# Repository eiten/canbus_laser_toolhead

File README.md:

# 🔥 Laser CANbus Toolhead PCB

> 🌍 **Languages:** [English](README.md) | [Deutsch](README.de.md)

A compact, robust toolhead board for Klipper-based laser engravers and cutters (CoreXY). This board integrates power supply, laser driver logic, CAN-Bus communication, and input shaping (ICM-20602) in the smallest possible space.

## 📚 Contents

<!-- @import "[TOC]" {cmd="toc" depthFrom=1 depthTo=6 orderedList=false} -->

<!-- code_chunk_output -->

- [🔥 Laser CANbus Toolhead PCB](#-laser-canbus-toolhead-pcb)
  - [📚 Contents](#-contents)
  - [✨ Features](#-features)
    - [🧠 Microcontroller](#-microcontroller)
    - [🔗 CAN-Bus Communication](#-can-bus-communication)
    - [📊 Input Shaping](#-input-shaping)
    - [⚡ Laser Power Control](#-laser-power-control)
    - [🎛️ Laser Signal Control](#️-laser-signal-control)
    - [🔌 Power Supply](#-power-supply)
    - [🚨 Diagnostics & Monitoring](#-diagnostics--monitoring)
  - [📋 Klipper Configuration](#-klipper-configuration)
    - [Basic MCU Setup](#basic-mcu-setup)
    - [Input Shaping (ICM-20602)](#input-shaping-icm-20602)
    - [Laser Control](#laser-control)
  - [🔌 Pinout & Connector Assignment](#-pinout--connector-assignment)
    - [J101 - Power & CAN Input (Micro-Fit 3.0, 2x2, THT)](#j101---power--can-input-micro-fit-30-2x2-tht)
    - [J102 - Laser Output (Micro-Fit 3.0, 1x3, THT)](#j102---laser-output-micro-fit-30-1x3-tht)
    - [Debug/Programming Header (Back Side)](#debugprogramming-header-back-side)
  - [🔧 Installation & Setup](#-installation--setup)
    - [1. CAN-Bus Configuration](#1-can-bus-configuration)
    - [2. Firmware Flash](#2-firmware-flash)
    - [3. Find UUID](#3-find-uuid)
  - [⚠️ Safety Notes](#️-safety-notes)
  - [🛠️ BOM (Bill of Materials) - Highlights](#️-bom-bill-of-materials---highlights)
  - [🛠️ Technical Specifications](#️-technical-specifications)
  - [📝 Changelog](#-changelog)
    - [Rev. 1](#rev-1)
    - [Rev. 0 (Initial Release)](#rev-0-initial-release)
  - [📚 Additional Resources](#-additional-resources)
  - [License](#license)

<!-- /code_chunk_output -->

## ✨ Features

### 🧠 Microcontroller
- **MCU:** STM32F072CBU6 (Cortex-M0, 48MHz, CAN-capable)
- **Stability:** 12MHz crystal for maximum CAN-Bus stability
- **Firmware:** Klipper-compatible

### 🔗 CAN-Bus Communication
- **Transceiver:** SN65HVD230 with ESD protection
- **Termination:** Split termination via solder jumper
- **Slope Control:** Switchable for EMI optimization

### 📊 Input Shaping
- **Sensor:** On-board ICM-20602 accelerometer/gyroscope (SPI)
- **Purpose:** Klipper resonance measurement for perfect print quality
- **Advantage:** Better availability and modern sensor technology

### ⚡ Laser Power Control
- **Circuit:** 24V / 6A High-Side Switch (CJAC70P06 P-MOSFET, 60V rated)
- **Peak Current:** 8A capability
- **Soft-Start:** Limits inrush current (Rise-time ~1.2ms)
- **Safety:** Hardware pull-down prevents unwanted activation
- **Limitation:** Max 6A limited by Micro Fit 3.0 connector with 0.75mm² wire

### 🎛️ Laser Signal Control
- **PWM:** 5V Level-shifted via 74AHCT1G125 buffer
- **Quality:** Clean edges, true hardware PWM via STM32 timer
- **Compatibility:** Common diode lasers

### 🔌 Power Supply
- **Input:** 24V with 250mA PTC fuse and SMF24A TVS diode
- **5V Rail:** MP2459 Buck converter (up to 60V input tolerant)
- **3.3V Rail:** XC6206 LDO for MCU and peripherals

### 🚨 Diagnostics & Monitoring
- **Power LEDs:** 24V In, 24V Sys, 5V, 3.3V
- **Status LEDs:** Laser Enable, Laser PWM, Heartbeat

## 📋 Klipper Configuration

### Basic MCU Setup
```ini
[mcu toolhead]
canbus_uuid: <your-uuid>  # Find with "ls /dev/serial/by-id/*" or "~/klippy-env/bin/python ~/klipper/scripts/canbus_query.py can0"

[temperature_sensor toolhead_mcu]
sensor_type: temperature_mcu
sensor_mcu: toolhead
```

### Input Shaping (ICM-20602)
```ini
[mpu9250]
cs_pin: toolhead:PA4
spi_bus: spi1
#axes_map: x,y,z  # Configure according to your printer orientation

[resonance_tester]
accel_chip: mpu9250
probe_points:
    150, 150, 20  # Adjust to your bed size
```

### Laser Control
```ini
# Laser PWM Signal
[output_pin laser_pwm]
pin: toolhead:PB14
pwm: True
cycle_time: 0.001          # 1kHz PWM frequency
shutdown_value: 0          # Safety: laser off during emergency

# Laser Enable (optional)
[output_pin laser_enable]
pin: toolhead:PB15
value: 0
shutdown_value: 0

# Heartbeat LED (optional)
[output_pin heartbeat]
pin: toolhead:PA9
pwm: True
cycle_time: 1.0
```

## 🔌 Pinout & Connector Assignment

### J101 - Power & CAN Input (Micro-Fit 3.0, 2x2, THT)
| Pin | Signal | Description |
|-----|---------|-------------|
| 1 | **+24V** | Main power input (High Current) |
| 2 | **GND** | Ground |
| 3 | **CAN_H** | CAN-Bus High Signal |
| 4 | **CAN_L** | CAN-Bus Low Signal |

### J102 - Laser Output (Micro-Fit 3.0, 1x3, THT)
| Pin | Signal | Description |
|-----|---------|-------------|
| 1 | **GND** | Laser Ground |
| 2 | **PWM** | 5V PWM Signal (Level-Shifted) |
| 3 | **+24V** | Switched Laser Power (Soft-Start) |

### Debug/Programming Header (Back Side)
| Pad | Pin | Signal | Function |
|-----|-----|---------|----------|
| 1 | - | **5V** | 5V Supply (from Programmer) |
| 2 | - | **3.3V** | VTref (Reference Voltage) |
| 3 | PA13 | **SWDIO** | Serial Wire Debug I/O |
| 4 | PA14 | **SWCLK** | Serial Wire Debug Clock |
| 5 | - | **NRST** | Reset Signal |
| 6 | - | **GND** | Ground |

> **💡 Bootloader Mode:** To force the STM32 into DFU/Bootloader mode (e.g., for initial flash with Katapult), bridge the **BOOT0** pad with **3.3V** during power-on.

## 🔧 Installation & Setup

### 1. CAN-Bus Configuration
- Set CAN-Bus termination according to position in network
- Baud rate: 1 Mbit/s (Klipper standard)

### 2. Firmware Flash
1. Put board into DFU mode (bridge BOOT0)
2. Compile Klipper for STM32F072 with CAN support
3. Flash firmware: `make flash FLASH_DEVICE=<dfu-device>`

### 3. Find UUID
```bash
~/klippy-env/bin/python ~/klipper/scripts/canbus_query.py can0
```

## ⚠️ Safety Notes

- **Laser Safety:** Always wear protective eyewear
- **Power Supply:** Only operate with 24V DC
- **Initial Setup:** Slowly ramp up laser power
- **Emergency:** Hardware pull-down ensures safe state

## 🛠️ BOM (Bill of Materials) - Highlights

| Component | Value/Type | Function | Package | Order Code |
|-----------|------------|----------|---------|------------|
| **U101** | STM32F072CBU6 | Main Microcontroller | UFQFPN-48 | STM32F072CBU6 |
| **U102** | MP2459GJ-Z | Buck Converter 24V→5V | TSOT-23-8 | MP2459GJ-Z |
| **U105** | SN65HVD230DR | CAN-Bus Transceiver | SOIC-8 | SN65HVD230DR |
| **U106** | ICM-20602 | 6-Axis IMU (Accelerometer/Gyroscope) | LGA-16 | ICM-20602 |
| **Q101** | CJAC70P06 | P-MOSFET (Laser Switch, 60V) | SOIC-8 | CJAC70P06 |
| **D101** | SMF24A | TVS Diode (Overvoltage Protection) | DO-214AC | SMF24A |
| **F101** | 1812L025 | PTC Fuse 250mA | 1812 | 1812L025 |
| **Y101** | 12MHz | Crystal for CAN Stability | HC-49/S | 12MHz Crystal |
| **J101/J102** | Micro-Fit 3.0 | THT Connectors | THT | Micro-Fit 3.0 THT |

## 🛠️ Technical Specifications

| Parameter | Value | Unit |
|-----------|-------|------|
| **Input Voltage** | 24 ± 2 | V |
| **Laser Current (max)** | 4 | A |
| **CAN Baud Rate** | 1 | Mbit/s |
| **PWM Frequency** | 1 | kHz |
| **Soft-Start Time** | ~1.2 | ms |
| **Operating Temperature** | -10 to +70 | °C |
| **Dimensions** | TBD | mm |

## 📝 Changelog

### Rev. 0.1
- **Transistor Upgrade:** Replaced MOSFET with CJAC70P06 (60V voltage rating)
- **Sensor Upgrade:** Changed from ADXL345 to ICM-20602 (better availability, modern 6-axis IMU)
- **Connector Change:** Micro Fit 3.0 connectors changed from SMD to THT mounting
- **Silkscreen Enhancement:** Added connector pin assignments to silkscreen for easier assembly
- **Layout Improvements:** Cleaned up component placement and optimized routing
- **Documentation:** Updated overview image to reflect current design
- **BOM Update:** Added component order numbers and updated production data
- **Production Files:** Updated assembly and production files with current components

### Rev. 0.0 (Initial Release)
- Initial PCB design with STM32F072CBU6 microcontroller
- CAN-Bus communication with SN65HVD230 transceiver
- 24V/4A laser power control with AO4407A MOSFET
- ADXL345 accelerometer for input shaping
- MP2459 buck converter for power supply

## 📚 Additional Resources

- [Klipper Documentation](https://www.klipper3d.org/Config_Reference.html)
- [CAN-Bus Setup Guide](https://www.klipper3d.org/CANBUS.html)
- [Input Shaping](https://www.klipper3d.org/Resonance_Compensation.html)
- [Katapult Firmware Flasher](https://github.com/Arksine/katapult)

## License

This project is licensed under the **Creative Commons Attribution-NonCommercial-ShareAlike 4.0 International License** (CC BY-NC-SA 4.0).

This means you are free to:
- **Share** — copy and redistribute the material in any medium or format
- **Adapt** — remix, transform, and build upon the material

Under the following terms:
- **Attribution** — You must give appropriate credit, provide a link to the license, and indicate if changes were made
- **NonCommercial** — You may not use the material for commercial purposes
- **ShareAlike** — If you remix, transform, or build upon the material, you must distribute your contributions under the same license

For the full license text, visit: https://creativecommons.org/licenses/by-nc-sa/4.0/

---

> **Note:** The original documentation is in German ([README.de.md](README.de.md)). This English version is a translation for international users.

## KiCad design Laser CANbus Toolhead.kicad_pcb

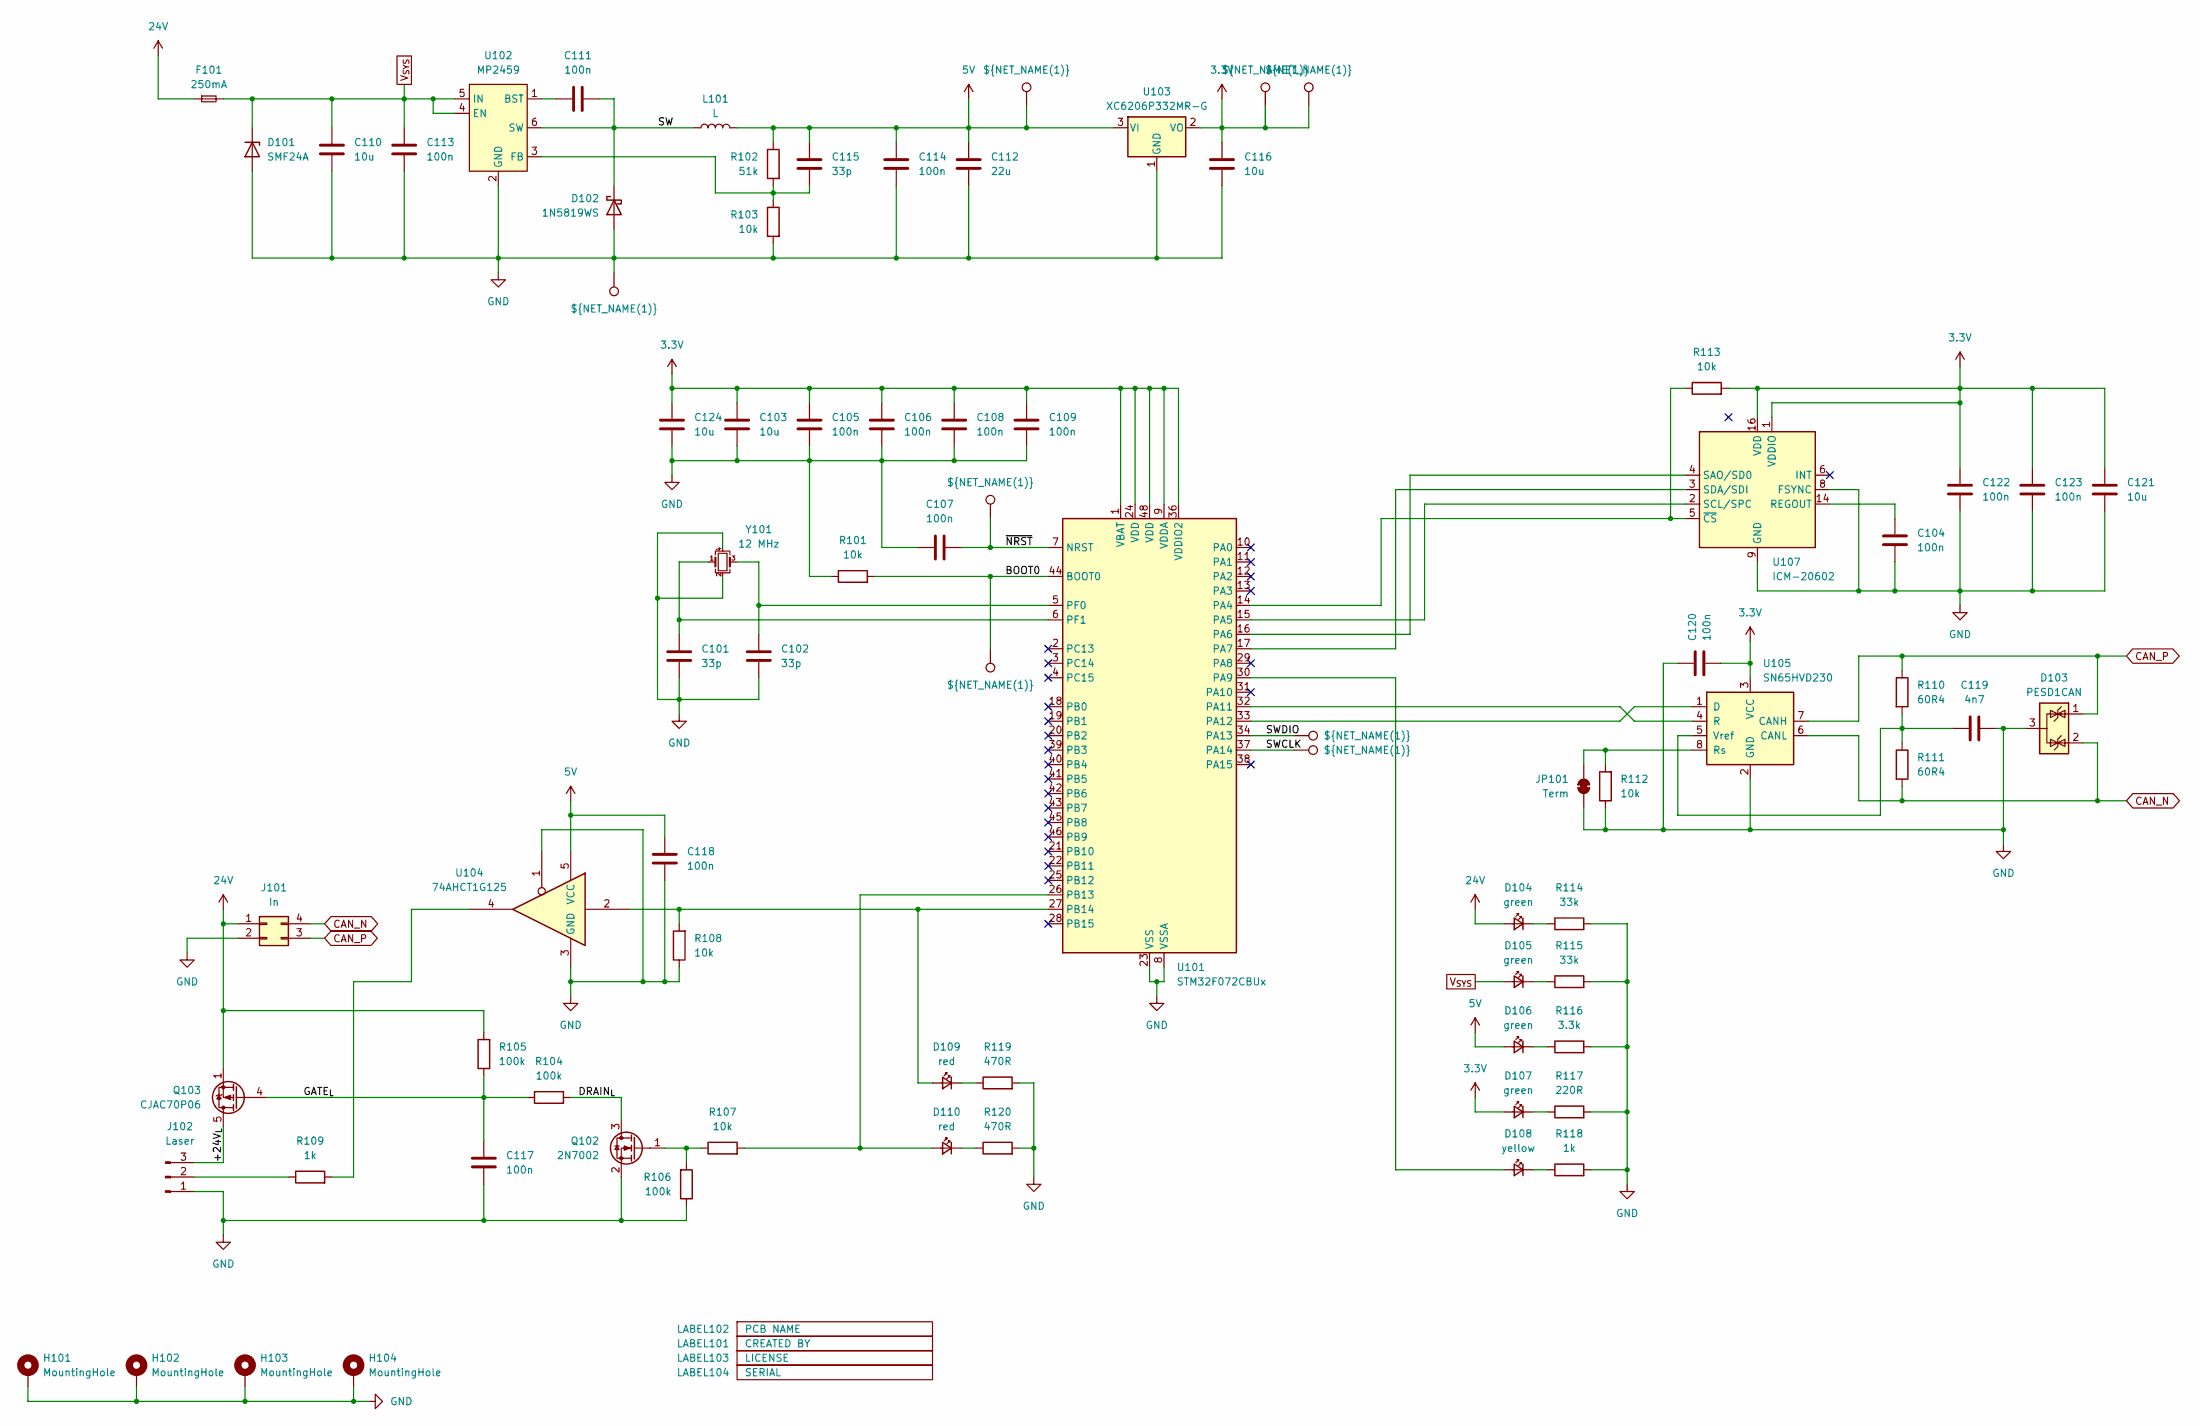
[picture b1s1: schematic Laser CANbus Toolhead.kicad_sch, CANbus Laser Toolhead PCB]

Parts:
C101, C102, C115: 33p; C_0402_1005Metric; Manufacturer Part # 0402CG330J500NT; LCSC Part # C1562
C103, C110, C116, C121, C124: 10u; C_0805_2012Metric; Manufacturer Part # GRM21BR61H106KE43L; LCSC Part # C440198
C104, C105, C106, C107, C108, C109, C111, C113, C114, C117, C118, C120, C122, C123: 100n; C_0402_1005Metric; Manufacturer Part # CL05B104KB54PNC; LCSC Part # C307331
C112: 22u; C_0805_2012Metric; Manufacturer Part # CL21A226MAQNNNE; LCSC Part # C45783
C119: 4n7; C_0402_1005Metric; Manufacturer Part # 0402B472K500NT; LCSC Part # C1538
D101: SMF24A; D_SOD-123F; Manufacturer Part # SMF24A; LCSC Part # C19077514
D102: 1N5819WS; D_SOD-323; Manufacturer Part # 1N5819WS; LCSC Part # C191023
D103: PESD1CAN; SOT-23; Manufacturer Part # PESD1CAN; LCSC Part # C343993
D104, D105, D106, D107: green; LED_0805_2012Metric; Manufacturer Part # KT-0805G; LCSC Part # C2297
D108: yellow; LED_0805_2012Metric; Manufacturer Part # KT-0805Y; LCSC Part # C2296
D109, D110: red; LED_0603_1608Metric; Manufacturer Part # KT-0603R; LCSC Part # C2286
F101: 250mA; Fuse_0805_2012Metric; Manufacturer Part # LUTE 0805L025/36XR; LCSC Part # C20608679
H101, H102, H103, H104: MountingHole; MountingHole_2.7mm_Pad_Via
J101: In; Molex_Micro-Fit_3.0_43045-0412_2x02_P3.00mm_Vertical; Manufacturer Part # M3025V-2x2P; LCSC Part # C492540
J102: Laser; Molex_Micro-Fit_3.0_43650-0315_1x03_P3.00mm_Vertical; Manufacturer Part # M3025V-1x3P; LCSC Part # C705183
JP101: Term; SolderJumper-2_P1.3mm_Bridged_RoundedPad1.0x1.5mm
L101: L; L_1008_2520Metric; Manufacturer Part # FTC252012S100MBCA; LCSC Part # C5832376
LABEL101: CREATED BY; EduardIten
LABEL102: PCB NAME; CLT Rev. xxx
LABEL103: LICENSE; CC_BY_NC_SA 4
LABEL104: SERIAL; SERIAL_No
Q102: 2N7002; SOT-23; Manufacturer Part # 2N7002; LCSC Part # C8545
Q103: CJAC70P06; AO_DFN-8-1EP_5.55x5.2mm_P1.27mm_EP4.12x4.6mm; Manufacturer Part # CJAC70P06; LCSC Part # C2898279
R101, R103, R107, R108, R112, R113: 10k; R_0402_1005Metric; Manufacturer Part # 0402WGF1002TCE; LCSC Part # C25744
R102: 51k; R_0402_1005Metric; Manufacturer Part # 0402WGF5102TCE; LCSC Part # C25794
R104, R105, R106: 100k; R_0402_1005Metric; Manufacturer Part # 0402WGF1003TCE; LCSC Part # C25741
R109, R118: 1k; R_0402_1005Metric; Manufacturer Part # 0402WGF1001TCE; LCSC Part # C11702
R110, R111: 60R4; R_0402_1005Metric; Manufacturer Part # 0402WGF604JTCE; LCSC Part # C60310
R114, R115: 33k; R_0402_1005Metric; Manufacturer Part # 0402WGF3302TCE; LCSC Part # C25779
R116: 3.3k; R_0402_1005Metric; Manufacturer Part # 0402WGF3301TCE; LCSC Part # C25890
R117: 220R; R_0402_1005Metric; Manufacturer Part # 0402WGF2200TCE; LCSC Part # C25091
R119, R120: 470R; R_0402_1005Metric; Manufacturer Part # 0402WGF4700TCE; LCSC Part # C25117
TP101, TP102, TP103, TP104, TP105, TP106, TP107, TP108: ${NET_NAME(1)}; NAMED_TEST_POINT
U101: STM32F072CBUx; QFN-48-1EP_7x7mm_P0.5mm_EP5.6x5.6mm; Manufacturer Part # STM32F072CBU6; LCSC Part # C92504
U102: MP2459; SOT-23-6; Manufacturer Part # MP2459GJ-Z; LCSC Part # C39578
U103: XC6206P332MR-G; SOT-23-3; Manufacturer Part # XC6206P332MR-G; LCSC Part # C5446
U104: 74AHCT1G125; SOT-353_SC-70-5; Manufacturer Part # SN74AHCT1G125DBVR; LCSC Part # C7484
U105: SN65HVD230; SOIC-8_3.9x4.9mm_P1.27mm; Manufacturer Part # SN65HVD230DR; LCSC Part # C12084
U107: ICM-20602; LGA-16_3x3mm_P0.5mm_LayoutBorder3x5y
Y101: 12 MHz; Crystal_SMD_3225-4Pin_3.2x2.5mm; Manufacturer Part # X322512MSB4SI; LCSC Part # C9002

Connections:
3.3V: C103.1, C105.1, C106.1, C108.1, C109.1, C116.1, C120.2, C121.1, C122.1, C123.1, C124.1, D107.2 (A), R113.2, TP102.1, TP108.1, U101.1 (VBAT), U101.9 (VDDA), U101.24 (VDD), U101.36 (VDDIO2), U101.48 (VDD), U103.2 (VO), U105.3 (VCC), U107.1 (VDDIO), U107.16 (VDD)
5V: C112.1, C114.1, C115.1, C118.1, D106.2 (A), L101.2, R102.1, TP101.1, U103.3 (VI), U104.5 (VCC)
24V: D104.2 (A), F101.1, J101.1, Q103.1 (S), Q103.2 (S), Q103.3 (S), R105.2
/+24V_{L}: J102.3, Q103.5 (D)
/BOOT0: R101.2, TP107.1, U101.44 (BOOT0)
/DRAIN_{L}: Q102.3 (D), R104.2
/GATE_{L}: C117.1, Q103.4 (G), R104.1, R105.1
/SW: C111.2, D102.1 (K), L101.1, U102.6 (SW)
/SWCLK: TP106.1, U101.37 (PA14)
/SWDIO: TP105.1, U101.34 (PA13)
/~NRST: C107.2, TP104.1, U101.7 (NRST)
CAN_N: D103.2 (K), J101.4, R111.2, U105.6 (CANL)
CAN_P: D103.1 (K), J101.3, R110.1, U105.7 (CANH)
GND: C101.2, C102.2, C103.2, C104.2, C105.2, C106.2, C107.1, C108.2, C109.2, C110.2, C112.2, C113.2, C114.2, C116.2, C117.2, C118.2, C119.2, C120.1, C121.2, C122.2, C123.2, C124.2, D101.2 (A), D102.2 (A), D103.3 (A), H101.1, H102.1, H103.1, H104.1, J101.2, J102.1, JP101.2 (B), Q102.2 (S), R101.1, R103.2, R106.1, R108.1, R112.1, R114.2, R115.2, R116.2, R117.2, R118.2, R119.2, R120.2, TP103.1, U101.8 (VSSA), U101.23 (VSS), U101.35 (VSS), U101.47 (VSS), U101.49 (VSS), U102.2 (GND), U103.1 (GND), U104.1, U104.3 (GND), U105.2 (GND), U107.8 (FSYNC), U107.9 (GND), U107.10 (GND), U107.11 (GND), U107.12 (GND), U107.13 (GND), U107.15 (GND), Y101.2, Y101.4
unnamed: D104.1 (K), R114.1
unnamed: D105.1 (K), R115.1
unnamed: D106.1 (K), R116.1
unnamed: D107.1 (K), R117.1
unnamed: D108.2 (A), U101.30 (PA9)
unnamed: D108.1 (K), R118.1
unnamed: D109.2 (A), R108.2, U101.27 (PB14), U104.2
unnamed: D109.1 (K), R119.1
unnamed: D110.2 (A), R107.2, U101.26 (PB13)
unnamed: D110.1 (K), R120.1
unnamed: J102.2, R109.1
unnamed: JP101.1 (A), R112.2, U105.8 (Rs)
unnamed: Q102.1 (G), R106.2, R107.1
unnamed: R109.2, U104.4
unnamed: R113.1, U101.14 (PA4), U107.5 (~CS)
unnamed: U101.15 (PA5), U107.2 (SCL/SPC)
unnamed: U101.16 (PA6), U107.4 (SAO/SD0)
unnamed: U101.17 (PA7), U107.3 (SDA/SDI)
unnamed: U101.32 (PA11), U105.4 (R)
unnamed: U101.33 (PA12), U105.1 (D)
unnamed: C102.1, U101.5 (PF0), Y101.3
unnamed: C101.1, U101.6 (PF1), Y101.1
unnamed: C111.1, U102.1 (BST)
unnamed: C115.2, R102.2, R103.1, U102.3 (FB)
unnamed: C119.1, R110.2, R111.1, U105.5 (Vref)
unnamed: C104.1, U107.14 (REGOUT)
V_{SYS}: C110.1, C113.1, D101.1 (K), D105.2 (A), F101.2, U102.4 (EN), U102.5 (IN)

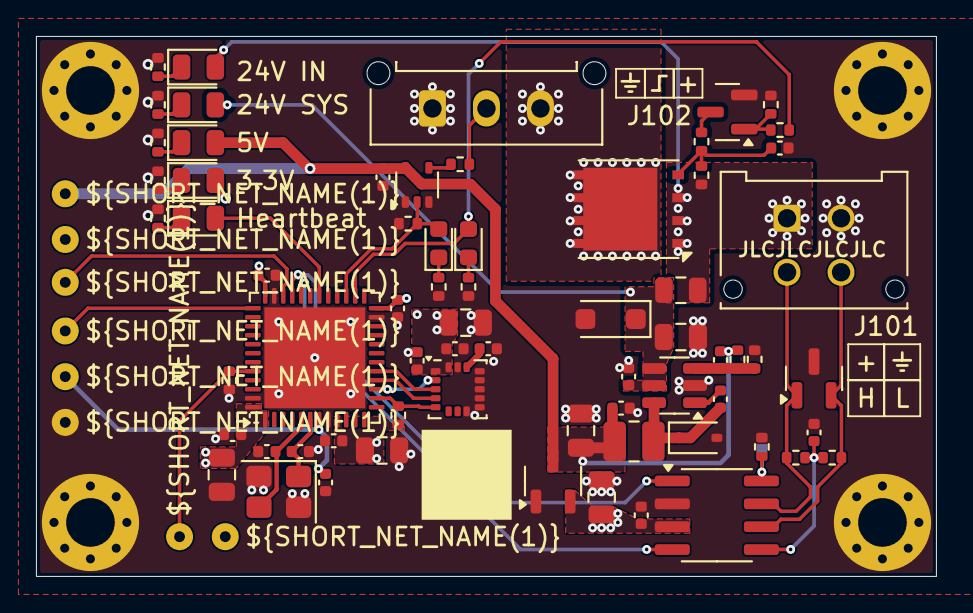
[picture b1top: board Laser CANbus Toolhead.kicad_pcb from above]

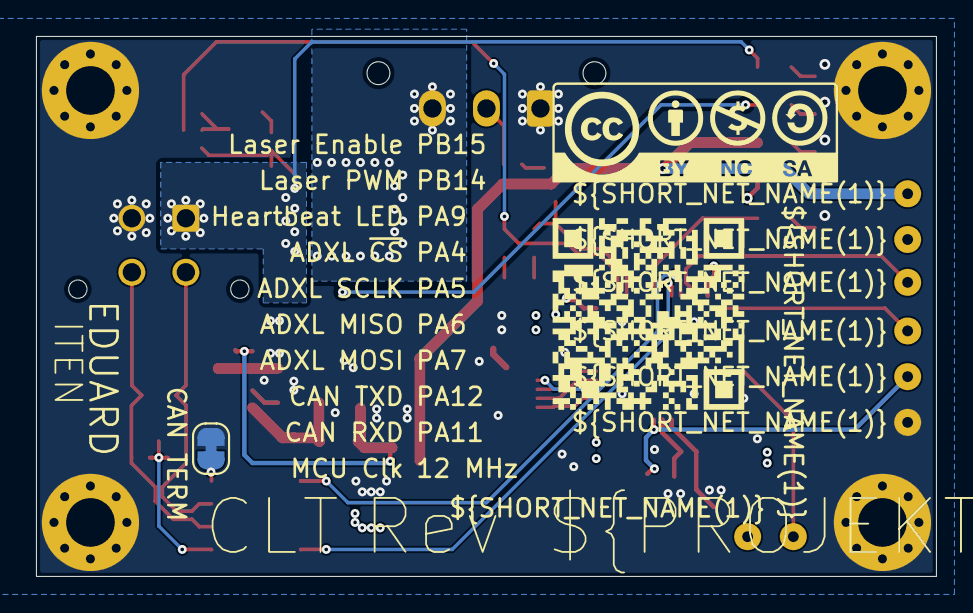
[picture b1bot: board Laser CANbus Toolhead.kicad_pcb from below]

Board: 4 copper layers, 50.0 x 30.0 mm, 84 parts (4 on the bottom side), 41 nets.

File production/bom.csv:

Designator,Footprint,Quantity,Value,LCSC Part #
"C101, C102, C115",0402,3,33p,C1562
"C103, C110, C116, C121, C124",0805,5,10u,C440198
"C104, C105, C106, C107, C108, C109, C111, C113, C114, C117, C118, C120, C122, C123",0402,14,100n,C307331
C112,0805,1,22u,C45783
C119,0402,1,4n7,C1538
D101,D_SOD-123F,1,SMF24A,C19077514
D102,D_SOD-323,1,1N5819WS,C191023
D103,SOT-23,1,PESD1CAN,C343993
"D104, D105, D106, D107",0805,4,green,C2297
D108,0805,1,yellow,C2296
"D109, D110",0603,2,red,C2286
F101,0805,1,250mA,C20608679
J101,Molex_Micro-Fit_3.0_43045-0412_2x02_P3.00mm_Vertical,1,In,C492540
J102,Molex_Micro-Fit_3.0_43650-0315_1x03_P3.00mm_Vertical,1,Laser,C705183
L101,1008,1,L,C5832376
Q102,SOT-23,1,2N7002,C8545
Q103,AO_DFN-8-1EP_5.55x5.2mm_P1.27mm_EP4.12x4.6mm,1,CJAC70P06,C2898279
"R101, R103, R107, R108, R112, R113",0402,6,10k,C25744
R102,0402,1,51k,C25794
"R104, R105, R106",0402,3,100k,C25741
"R109, R118",0402,2,1k,C11702
"R110, R111",0402,2,60R4,C60310
"R114, R115",0402,2,33k,C25779
R116,0402,1,3.3k,C25890
R117,0402,1,220R,C25091
"R119, R120",0402,2,470R,C25117
U101,QFN-48-1EP_7x7mm_P0.5mm_EP5.6x5.6mm,1,STM32F072CBUx,C92504
U102,SOT-23-6,1,MP2459,C39578
U103,SOT-23-3,1,XC6206P332MR-G,C5446
U104,SOT-353_SC-70-5,1,74AHCT1G125,C7484
U105,SOIC-8_3.9x4.9mm_P1.27mm,1,SN65HVD230,C12084
U107,LGA-16_3x3mm_P0.5mm_LayoutBorder3x5y,1,ICM-20602,
Y101,Crystal_SMD_3225-4Pin_3.2x2.5mm,1,12 MHz,C9002

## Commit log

2025-11-25 Added PCB image
2025-11-26 feat: Major hardware upgrade to Rev. 1
    - Replace MOSFET with CJAC70P06 (60V voltage rating)
    - Upgrade sensor from ADXL345 to ICM-20602 (better availability, 6-axis IMU)
    - Change Micro Fit 3.0 connectors from SMD to THT mounting
    - Add connector pinouts to silkscreen for easier assembly
    - Clean up component placement and optimize layout
    - Update overview image to reflect current design
2025-11-26 Update documentation: improve language hints and add CC BY-NC-SA 4.0 license
    - Updated language selection format to match ROCK 5 CANbus HAT style
    - Added comprehensive CC BY-NC-SA 4.0 license section to both README files
    - Updated project image with new raytraced version
    - Improved documentation consistency across projects
2025-12-09 docs: Update version numbering to semantic versioning (Rev. 0.0/0.1)
    - Rename Rev. 0 to Rev. 0.0 (initial release)
    - Rename Rev. 1 to Rev. 0.1 (major hardware upgrade)
    - Update all documentation (README and CHANGELOG files)
    - Create new git tags with proper semantic versioning
2025-12-09 feat: Complete project cleanup and Rev. 0.3 updates
    - Remove unused schematic files (mcu.kicad_sch, PWR.kicad_sch)
    - Update version numbering to semantic versioning (Rev. 0.0/0.1)
    - Add comprehensive changelog documentation in both languages
    - Create separate CHANGELOG.md and CHANGELOG.de.md files
    - Update PCB to Rev. 0.3 with layout optimizations
    - Professional 4-layer PCB design with optimal via stitching
